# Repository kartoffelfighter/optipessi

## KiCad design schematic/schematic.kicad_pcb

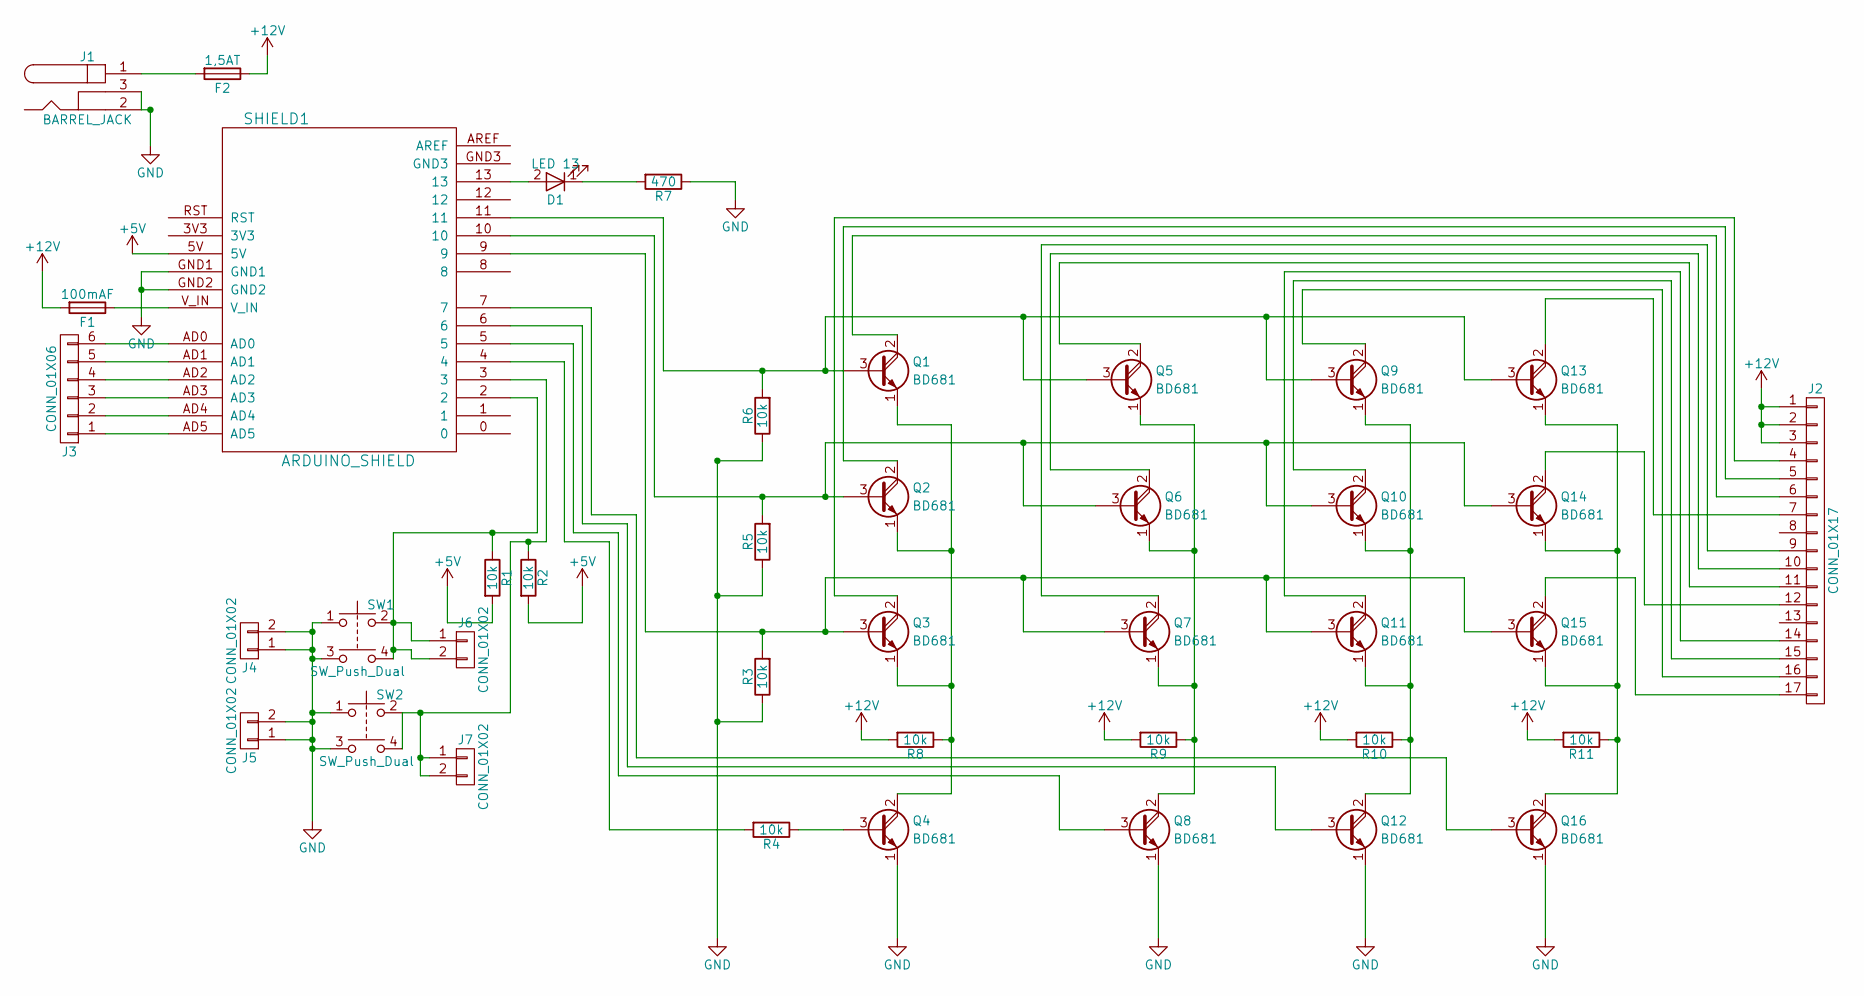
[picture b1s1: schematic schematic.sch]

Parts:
D1: LED 13; LED_0805_HandSoldering
F1: 100mAF; Fuse_SMD1206_Wave
F2: 1,5AT; Fuse_SMD1206_Wave
J1: BARREL_JACK
J2: CONN_01X17; Pin_Header_Straight_1x17_Pitch2.54mm
J3: CONN_01X06; Pin_Header_Straight_1x06_Pitch2.54mm
J4, J5, J6, J7: CONN_01X02; Pin_Header_Straight_1x02_Pitch2.54mm
Q1, Q2, Q3, Q4, Q5, Q6, Q7, Q8, Q9, Q10, Q11, Q12, Q13, Q14, Q15, Q16: BD681; TO-126_Horizontal
R1, R2, R3, R4, R5, R6, R8, R9, R10, R11: 10k; R_0805_HandSoldering
R7: 470; R_0805_HandSoldering
SHIELD1: ARDUINO_SHIELD; ARDUINO SHIELD
SW1, SW2: SW_Push_Dual; SW_TH_Tactile_Omron_B3F-10xx

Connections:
+5V: R1.2, R2.2, SHIELD1.5V
+12V: F1.2, F2.1, J2.1, J2.2, J2.3, R8.2, R9.2, R10.2, R11.2
GND: J1.2, J1.3, J4.1, J4.2, J5.1, J5.2, Q4.1 (E), Q8.1 (E), Q12.1 (E), Q16.1 (E), R3.1, R5.1, R6.1, R7.1, SHIELD1.GND1, SHIELD1.GND2, SW1.1, SW1.3, SW2.1, SW2.3
unnamed: D1.1 (K), R7.2
unnamed: D1.2 (A), SHIELD1.13
unnamed: F1.1, SHIELD1.V_IN
unnamed: F2.2, J1.1
unnamed: J2.4, Q3.2 (C)
unnamed: J2.5, Q2.2 (C)
unnamed: J2.6, Q1.2 (C)
unnamed: J2.7, Q13.2 (C)
unnamed: J2.9, Q7.2 (C)
unnamed: J2.10, Q6.2 (C)
unnamed: J2.11, Q5.2 (C)
unnamed: J2.12, Q14.2 (C)
unnamed: J2.14, Q11.2 (C)
unnamed: J2.15, Q10.2 (C)
unnamed: J2.16, Q9.2 (C)
unnamed: J2.17, Q15.2 (C)
unnamed: J3.1, SHIELD1.AD5
unnamed: J3.2, SHIELD1.AD4
unnamed: J3.3, SHIELD1.AD3
unnamed: J3.4, SHIELD1.AD2
unnamed: J3.5, SHIELD1.AD1
unnamed: J3.6, SHIELD1.AD0
unnamed: J6.1, J6.2, R1.1, SHIELD1.2, SW1.2, SW1.4
unnamed: J7.1, J7.2, R2.1, SHIELD1.3, SW2.2, SW2.4
unnamed: Q1.1 (E), Q2.1 (E), Q3.1 (E), Q4.2 (C), R8.1
unnamed: Q1.3 (B), Q5.3 (B), Q9.3 (B), Q13.3 (B), R6.2, SHIELD1.11
unnamed: Q4.3 (B), R4.1
unnamed: Q5.1 (E), Q6.1 (E), Q7.1 (E), Q8.2 (C), R9.1
unnamed: Q8.3 (B), SHIELD1.5
unnamed: Q9.1 (E), Q10.1 (E), Q11.1 (E), Q12.2 (C), R10.1
unnamed: Q2.3 (B), Q6.3 (B), Q10.3 (B), Q14.3 (B), R5.2, SHIELD1.10
unnamed: Q3.3 (B), Q7.3 (B), Q11.3 (B), Q15.3 (B), R3.2, SHIELD1.9
unnamed: Q12.3 (B), SHIELD1.6
unnamed: Q13.1 (E), Q14.1 (E), Q15.1 (E), Q16.2 (C), R11.1
unnamed: Q16.3 (B), SHIELD1.7
unnamed: R4.2, SHIELD1.4

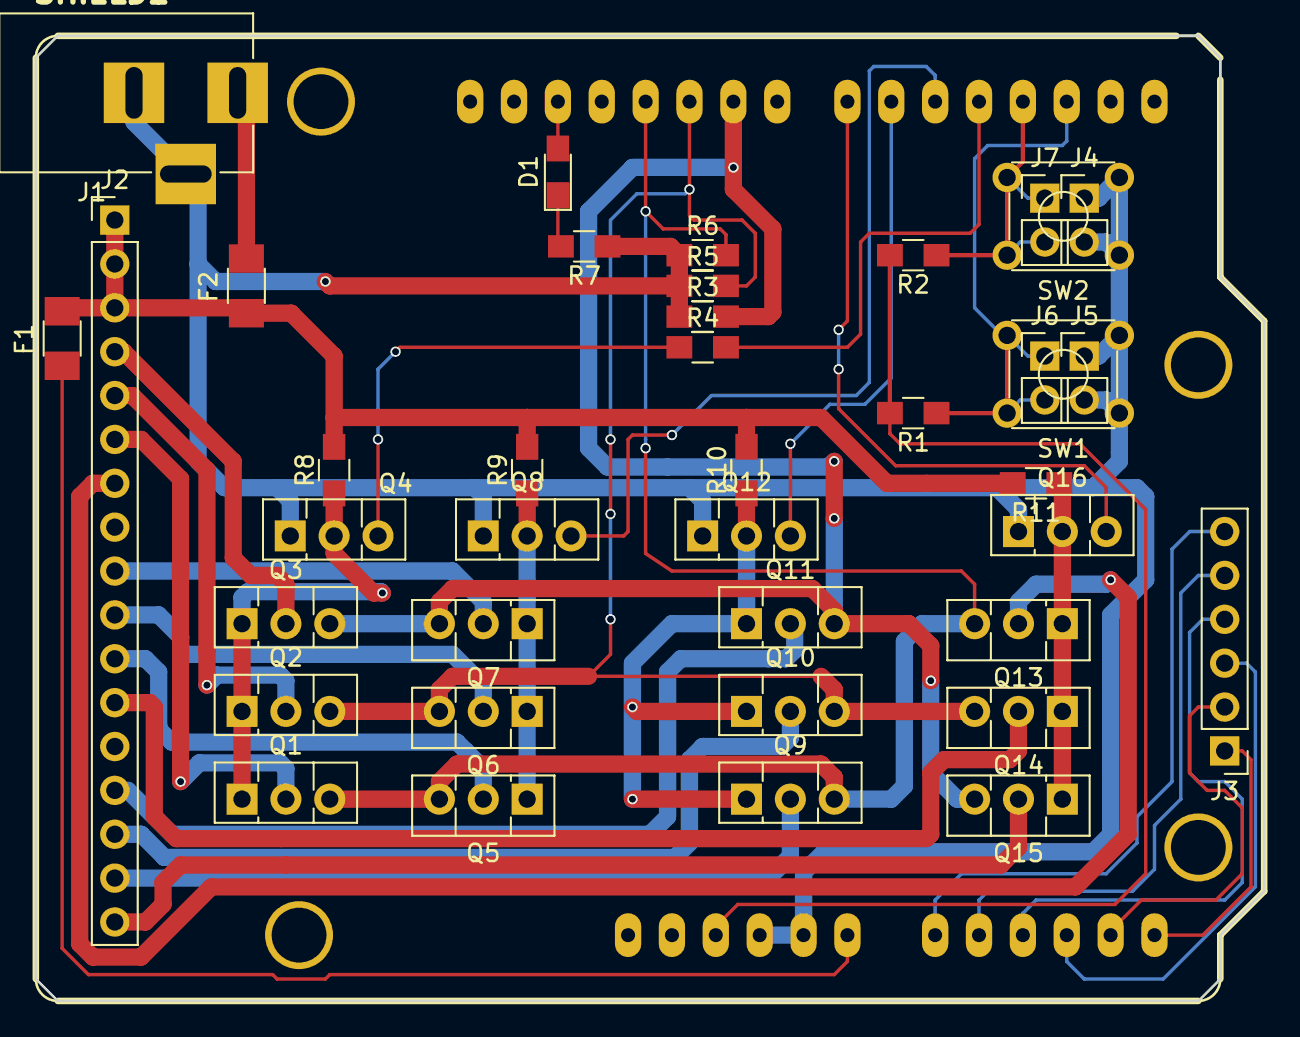
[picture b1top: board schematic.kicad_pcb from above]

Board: 2 copper layers, 71.1 x 55.9 mm, 40 parts (0 on the bottom side), 39 nets.

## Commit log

2018-01-11 initial
2018-01-11 schrift des plakats als jpeg für 3d modell
2018-01-16 initial version
2018-01-19 pcb v2 - added resistors, changed connectors, changed tracks
2018-01-19 !WIP! first running code
    loop-based LED show controlled by interrupts
2018-06-23 light show now automatically converts seconds to minutes
    added counter for runtime
    added incoming values from serial
2018-06-23 added reset to zero opti & pessi
2018-06-23 deleted delays
2018-06-23 added standby function, added serial function description
2018-06-23 added serial remote control
2018-06-23 added release hex file
